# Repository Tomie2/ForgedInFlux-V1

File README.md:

# ForgedInFlux V1
 The ultimate Brushed DC Motor Model.

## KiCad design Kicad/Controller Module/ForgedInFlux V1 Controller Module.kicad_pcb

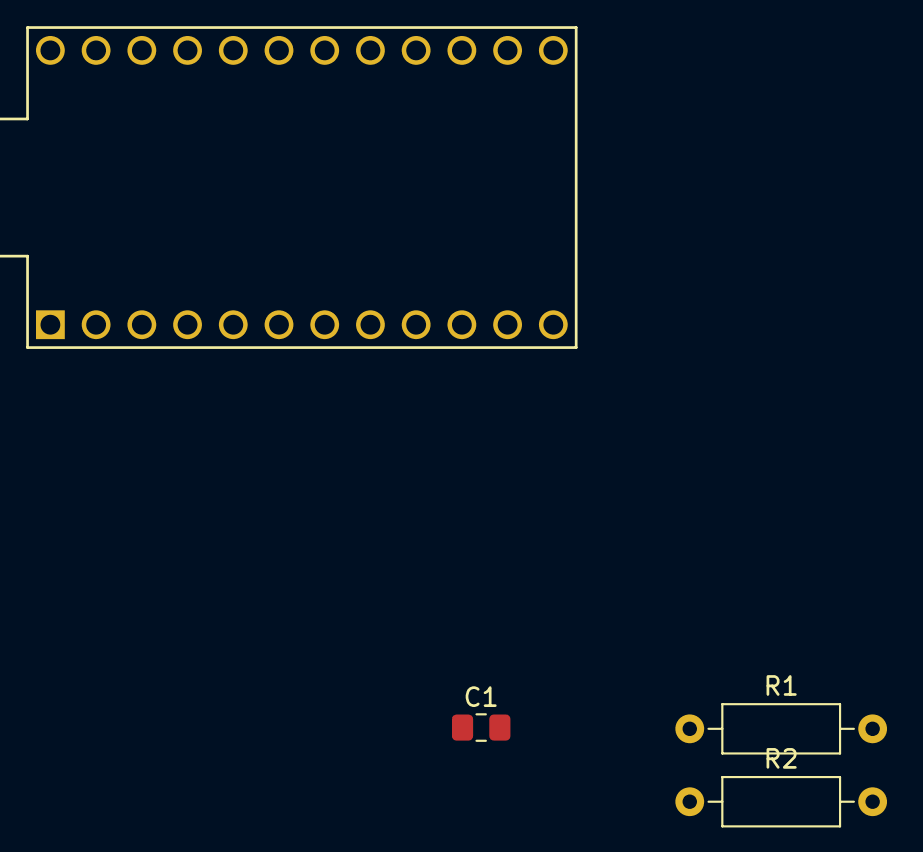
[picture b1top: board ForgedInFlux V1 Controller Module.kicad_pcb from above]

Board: 2 copper layers, 4 parts (0 on the bottom side), 2 nets, no tracks yet.

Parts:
C1: 0.1uF; C_0805_2012Metric_Pad1.18x1.45mm_HandSolder
R1: 47K; R_Axial_DIN0207_L6.3mm_D2.5mm_P10.16mm_Horizontal
R2: 4.7K; R_Axial_DIN0207_L6.3mm_D2.5mm_P10.16mm_Horizontal
U1: ProMicro

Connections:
GND: C1.2, R2.2, U1.23 (GND)
unnamed: C1.1, R1.2, R2.1, U1.17 (A0)

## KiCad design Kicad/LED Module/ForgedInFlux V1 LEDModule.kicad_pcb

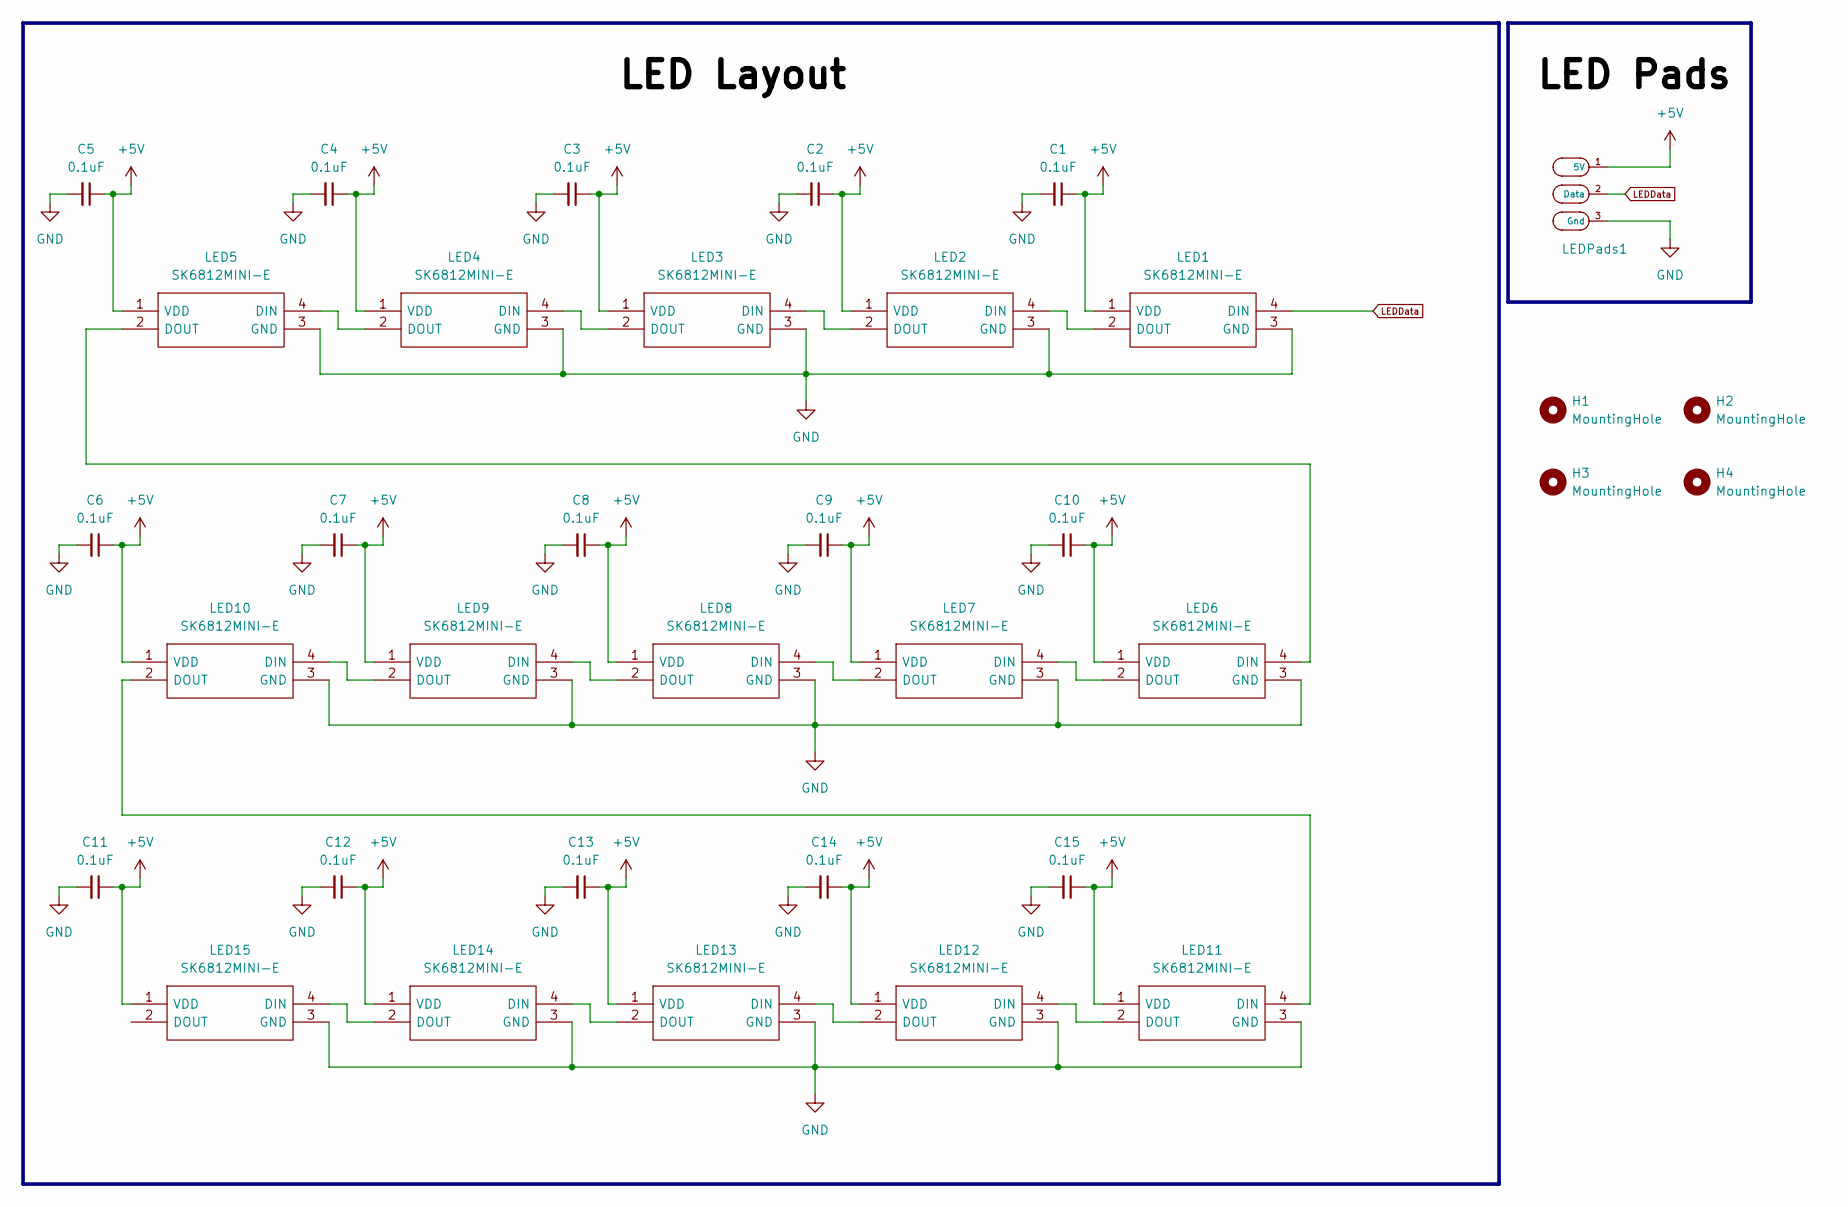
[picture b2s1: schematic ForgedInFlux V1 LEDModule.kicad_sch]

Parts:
C1, C2, C3, C4, C5, C6, C7, C8, C9, C10, C11, C12, C13, C14, C15: 0.1uF; C_0805_2012Metric_Pad1.18x1.45mm_HandSolder
H1, H2, H3, H4: MountingHole; MountingHole_3.2mm_M3_Pad
LED1, LED2, LED3, LED4, LED5, LED6, LED7, LED8, LED9, LED10, LED11, LED12, LED13, LED14, LED15: SK6812MINI-E; SK6812-MINI-E; Manufacturer_Part_Number SK6812MINI-E
LEDPads1: Led Pads

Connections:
+5V: C1.1, C2.1, C3.1, C4.1, C5.1, C6.1, C7.1, C8.1, C9.1, C10.1, C11.1, C12.1, C13.1, C14.1, C15.1, LED1.1 (VDD), LED2.1 (VDD), LED3.1 (VDD), LED4.1 (VDD), LED5.1 (VDD), LED6.1 (VDD), LED7.1 (VDD), LED8.1 (VDD), LED9.1 (VDD), LED10.1 (VDD), LED11.1 (VDD), LED12.1 (VDD), LED13.1 (VDD), LED14.1 (VDD), LED15.1 (VDD), LEDPads1.1 (5V)
GND: C1.2, C2.2, C3.2, C4.2, C5.2, C6.2, C7.2, C8.2, C9.2, C10.2, C11.2, C12.2, C13.2, C14.2, C15.2, LED1.3 (GND), LED2.3 (GND), LED3.3 (GND), LED4.3 (GND), LED5.3 (GND), LED6.3 (GND), LED7.3 (GND), LED8.3 (GND), LED9.3 (GND), LED10.3 (GND), LED11.3 (GND), LED12.3 (GND), LED13.3 (GND), LED14.3 (GND), LED15.3 (GND), LEDPads1.3 (Gnd)
LEDData: LED1.4 (DIN), LEDPads1.2 (Data)
unnamed: LED1.2 (DOUT), LED2.4 (DIN)
unnamed: LED2.2 (DOUT), LED3.4 (DIN)
unnamed: LED3.2 (DOUT), LED4.4 (DIN)
unnamed: LED4.2 (DOUT), LED5.4 (DIN)
unnamed: LED5.2 (DOUT), LED6.4 (DIN)
unnamed: LED6.2 (DOUT), LED7.4 (DIN)
unnamed: LED7.2 (DOUT), LED8.4 (DIN)
unnamed: LED8.2 (DOUT), LED9.4 (DIN)
unnamed: LED9.2 (DOUT), LED10.4 (DIN)
unnamed: LED10.2 (DOUT), LED11.4 (DIN)
unnamed: LED11.2 (DOUT), LED12.4 (DIN)
unnamed: LED12.2 (DOUT), LED13.4 (DIN)
unnamed: LED13.2 (DOUT), LED14.4 (DIN)
unnamed: LED14.2 (DOUT), LED15.4 (DIN)

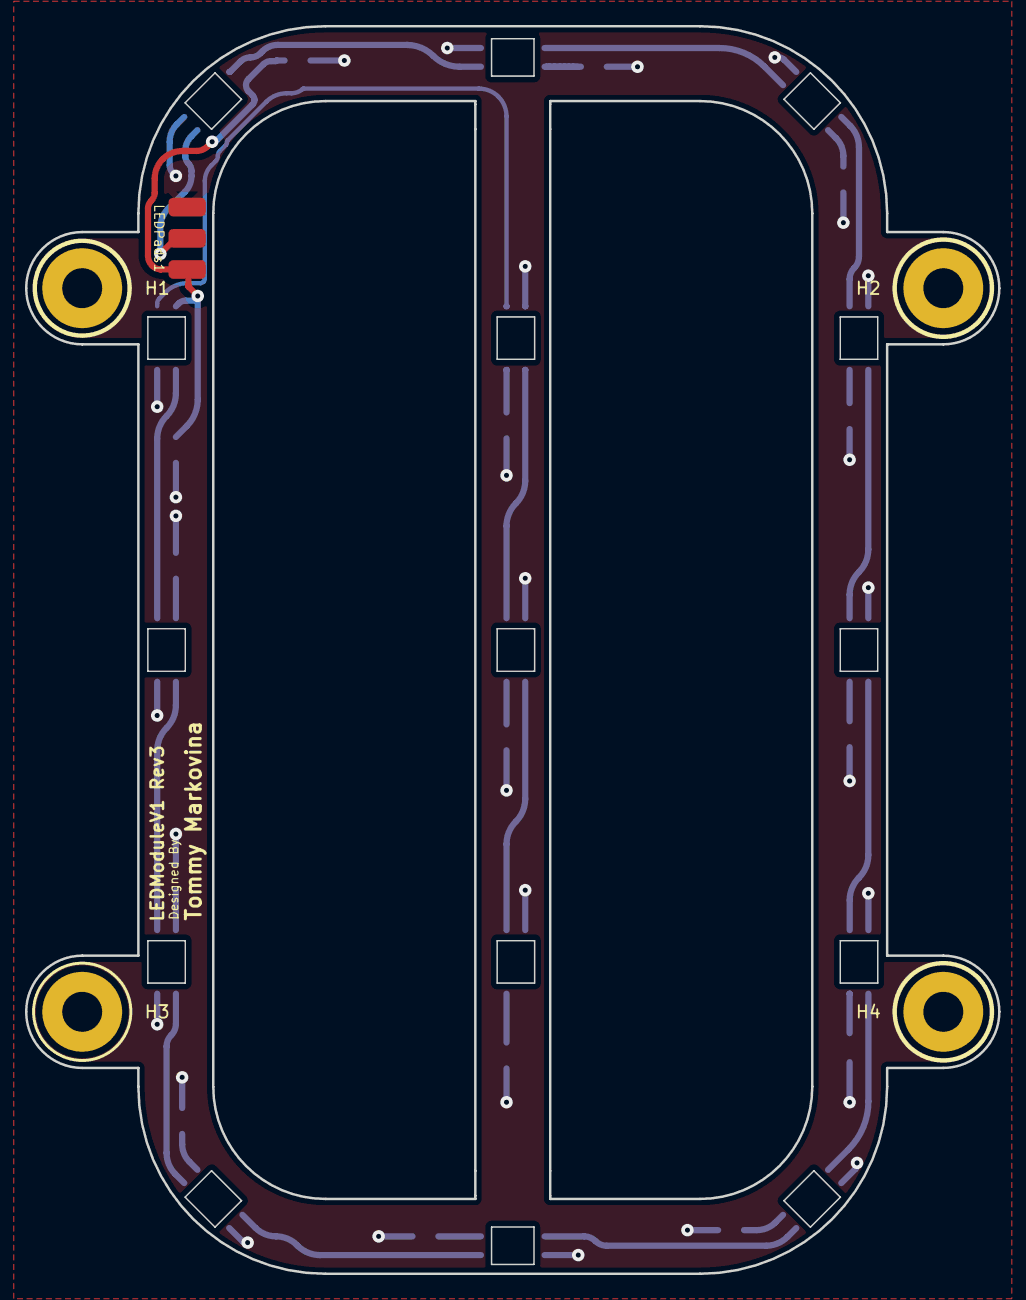
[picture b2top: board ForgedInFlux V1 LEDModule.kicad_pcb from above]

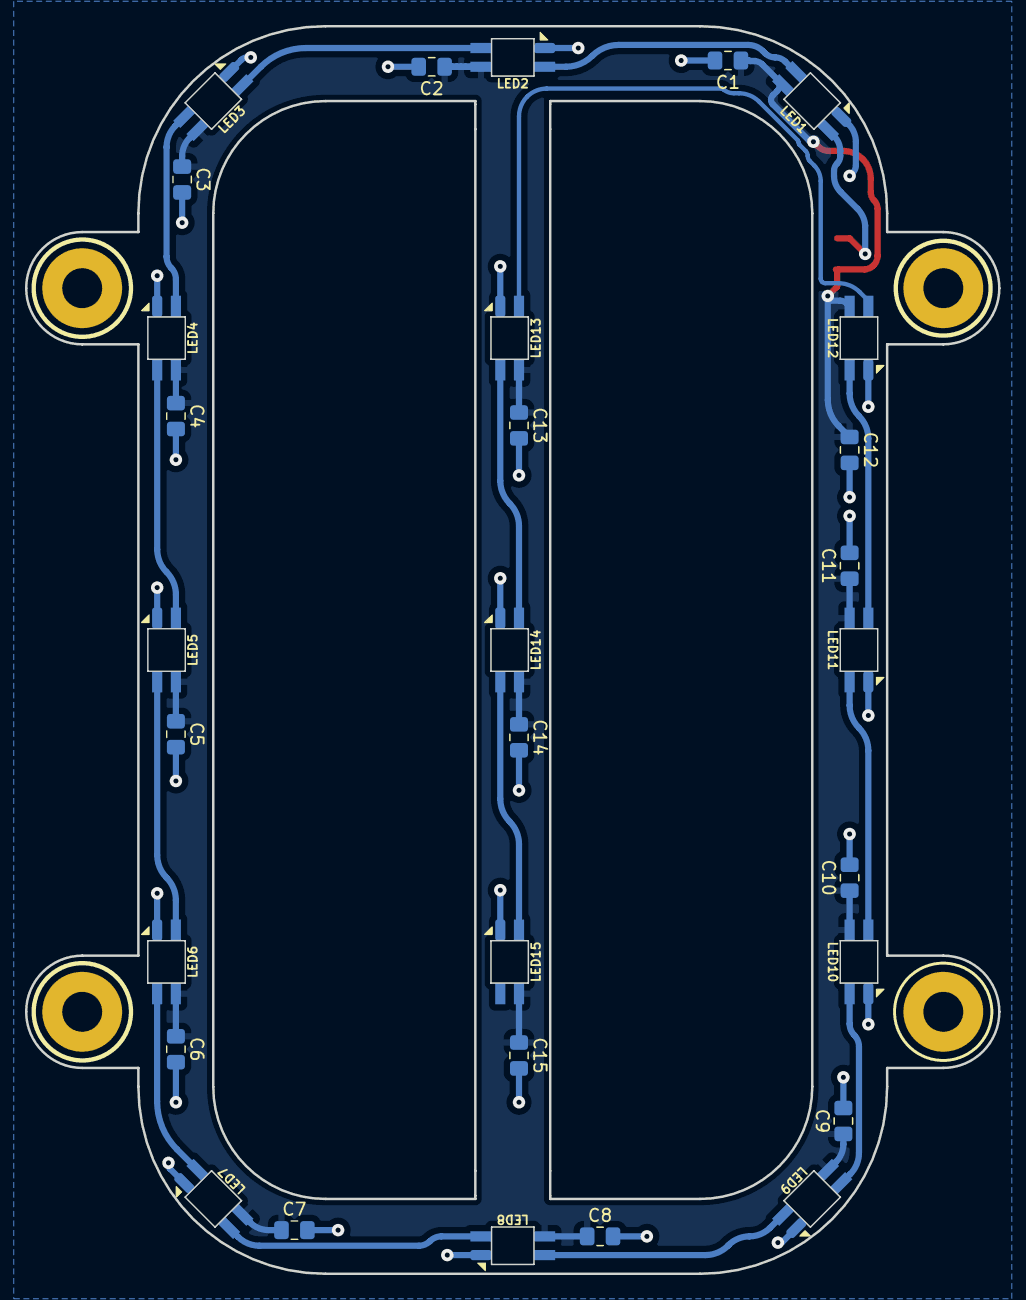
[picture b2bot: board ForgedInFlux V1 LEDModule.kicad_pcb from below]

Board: 2 copper layers, 78.0 x 100.0 mm, 35 parts (30 on the bottom side), 17 nets.

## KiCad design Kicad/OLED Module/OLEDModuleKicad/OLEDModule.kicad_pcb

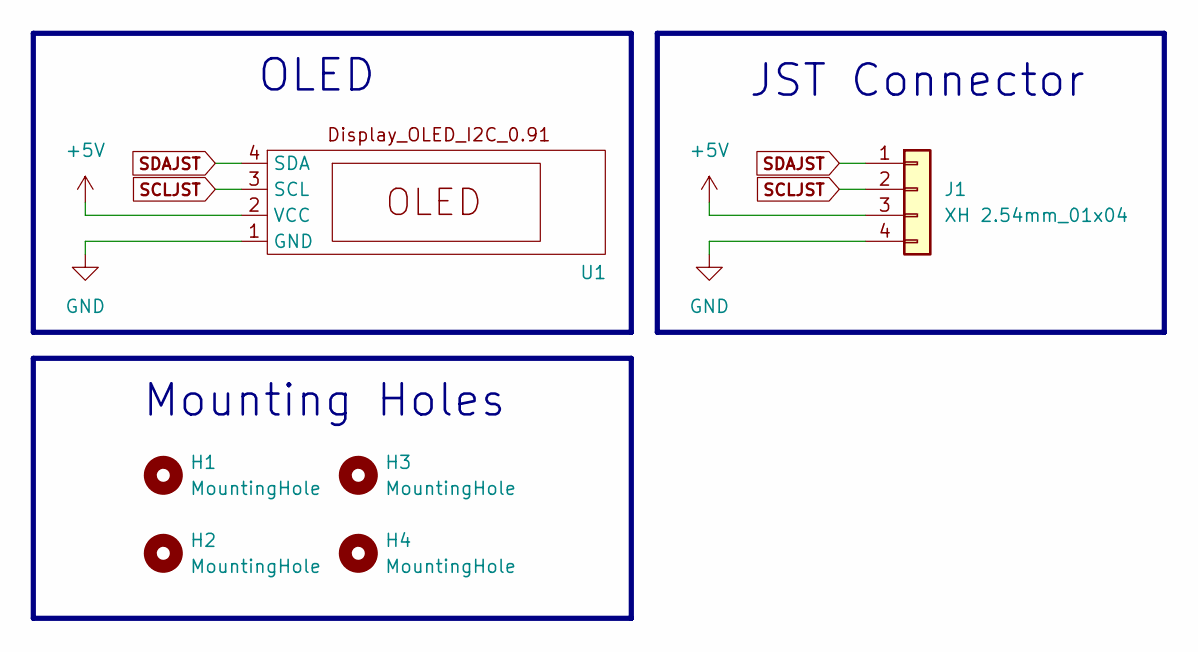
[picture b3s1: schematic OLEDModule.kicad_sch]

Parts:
H1, H2, H3, H4: MountingHole; MountingHole_3.2mm_M3_Pad
J1: XH 2.54mm_01x04; JST_XH_2.54_01x04_Vertical
U1: SSD1306-OLED-4pin-128x32

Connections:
+5V: J1.3, U1.2 (VCC)
GND: J1.4, U1.1 (GND)
SCLJST: J1.2, U1.3 (SCL)
SDAJST: J1.1, U1.4 (SDA)

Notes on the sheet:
OLED
JST Connector
Mounting Holes

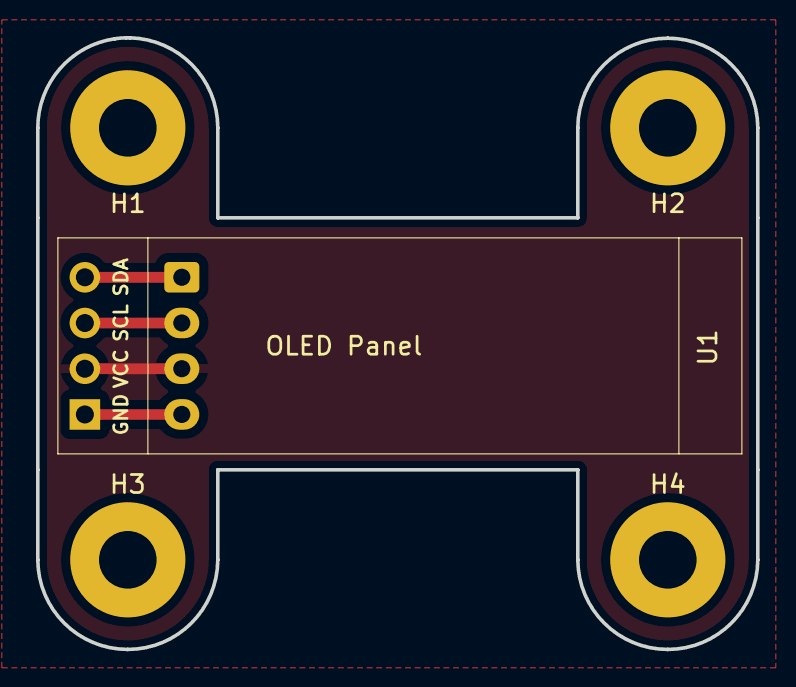
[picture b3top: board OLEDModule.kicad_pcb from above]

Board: 2 copper layers, 40.0 x 34.0 mm, 6 parts (1 on the bottom side), 4 nets.

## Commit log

2024-03-10 Project Initialized
    Setup Directories and file paths for Kicad files, as well as folders for any related graphics and fusion360 files along with their STL files.
2024-03-10 LEDModule Initialized
    Decided on using Sk6812 Based LEDS as WS2812B are out of stock on JLCPCB.
    Layed out all 15 LEDS on LED Module Schematic. Exported SVG of Edgecuts for PCB from Fusion360 and used Inkscape to convert them to a DXF file for use as edge cuts in the PCB Editor.
2024-03-11 Edited Schematic
2024-03-11 Started Creating LEDModulePCB
    - Edge cuts recompleted with adjusted dimensions
    - Created custom footprints and schematic symbol for LED Pads
    - Completed Schematic
    - Layed out parts components onto a pcb and done rough wire tracing.
2024-03-11 Updates to schematic
    - Changed Capacitor from Series to Parrallel
    - Thickened PCB Traces
    - Changed GND fill layers to 1 GND and 1 5V
2024-03-12 Continued Development of Design
    LEDModule Schematic and PCB need to be reworked for accommodation of hand soldered parts
2024-03-13 Redesigned PCB
    - Components changed for hand solderable parts
    - Resistor in future will need to be exchanged for one that can handle more wattage.
    - In future more clearance will be needed for top right LED.
2024-03-13 Updated design
    - Full 1w SMD Resistor
    - Satsified tolerances on LEDS and board edgecuts.
2024-03-14 Changes
    - removed 1w resistor (not required for sk6812 mini-e leds)
    added mounting holes that align with control unit internal standoffs
2024-03-14 Refresh
2024-03-16 Major Updates
    - Created OLEDModule
    - Finished LEDModule (Orderd few days ago)
    - Started working on ControlModule
